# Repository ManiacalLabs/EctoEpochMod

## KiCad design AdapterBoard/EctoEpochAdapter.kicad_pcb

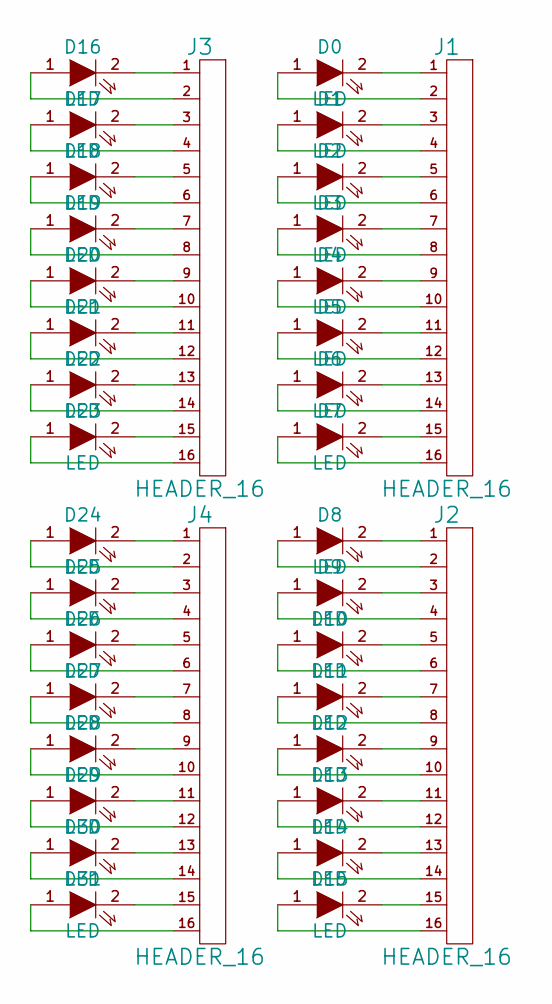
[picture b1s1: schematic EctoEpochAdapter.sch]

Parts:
D0, D1, D2, D3, D4, D5, D6, D7, D8, D9, D10, D11, D12, D13, D14, D15, D16, D17, D18, D19, D20, D21, D22, D23, D24, D25, D26, D27, D28, D29, D30, D31: LED
J1, J2, J3, J4: HEADER_16

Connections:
unnamed: D19.1 (A), J3.8
unnamed: D22.1 (A), J3.14
unnamed: D23.2 (K), J3.15
unnamed: D23.1 (A), J3.16
unnamed: D16.2 (K), J3.1
unnamed: D16.1 (A), J3.2
unnamed: D17.2 (K), J3.3
unnamed: D17.1 (A), J3.4
unnamed: D18.2 (K), J3.5
unnamed: D18.1 (A), J3.6
unnamed: D19.2 (K), J3.7
unnamed: D22.2 (K), J3.13
unnamed: D20.2 (K), J3.9
unnamed: D20.1 (A), J3.10
unnamed: D21.2 (K), J3.11
unnamed: D21.1 (A), J3.12
unnamed: D27.1 (A), J4.8
unnamed: D30.1 (A), J4.14
unnamed: D31.2 (K), J4.15
unnamed: D31.1 (A), J4.16
unnamed: D24.2 (K), J4.1
unnamed: D24.1 (A), J4.2
unnamed: D25.2 (K), J4.3
unnamed: D25.1 (A), J4.4
unnamed: D26.2 (K), J4.5
unnamed: D26.1 (A), J4.6
unnamed: D27.2 (K), J4.7
unnamed: D30.2 (K), J4.13
unnamed: D28.2 (K), J4.9
unnamed: D28.1 (A), J4.10
unnamed: D29.2 (K), J4.11
unnamed: D29.1 (A), J4.12
unnamed: D3.1 (A), J1.8
unnamed: D6.1 (A), J1.14
unnamed: D7.2 (K), J1.15
unnamed: D7.1 (A), J1.16
unnamed: D0.2 (K), J1.1
unnamed: D0.1 (A), J1.2
unnamed: D1.2 (K), J1.3
unnamed: D1.1 (A), J1.4
unnamed: D2.2 (K), J1.5
unnamed: D2.1 (A), J1.6
unnamed: D3.2 (K), J1.7
unnamed: D6.2 (K), J1.13
unnamed: D4.2 (K), J1.9
unnamed: D4.1 (A), J1.10
unnamed: D5.2 (K), J1.11
unnamed: D5.1 (A), J1.12
unnamed: D11.1 (A), J2.8
unnamed: D14.1 (A), J2.14
unnamed: D15.2 (K), J2.15
unnamed: D15.1 (A), J2.16
unnamed: D8.2 (K), J2.1
unnamed: D8.1 (A), J2.2
unnamed: D9.2 (K), J2.3
unnamed: D9.1 (A), J2.4
unnamed: D10.2 (K), J2.5
unnamed: D10.1 (A), J2.6
unnamed: D11.2 (K), J2.7
unnamed: D14.2 (K), J2.13
unnamed: D12.2 (K), J2.9
unnamed: D12.1 (A), J2.10
unnamed: D13.2 (K), J2.11
unnamed: D13.1 (A), J2.12

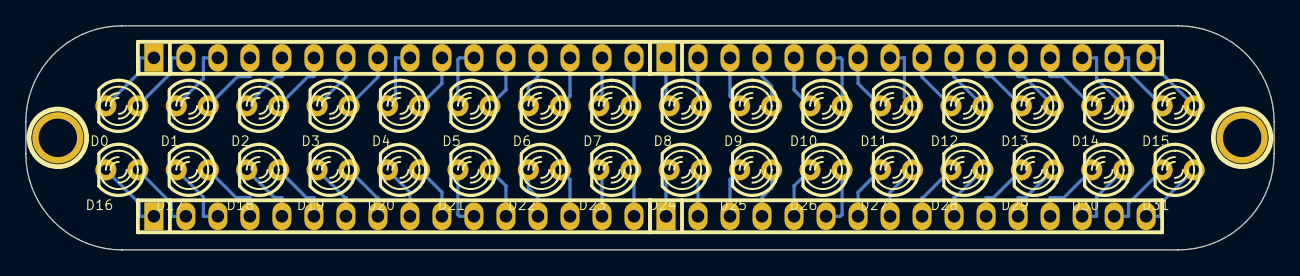
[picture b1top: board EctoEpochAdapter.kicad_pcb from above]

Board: 2 copper layers, 99.1 x 17.8 mm, 38 parts (0 on the bottom side), 64 nets.

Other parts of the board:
1PIN1: PL; 1pin
1PIN2: PR; 1pin
